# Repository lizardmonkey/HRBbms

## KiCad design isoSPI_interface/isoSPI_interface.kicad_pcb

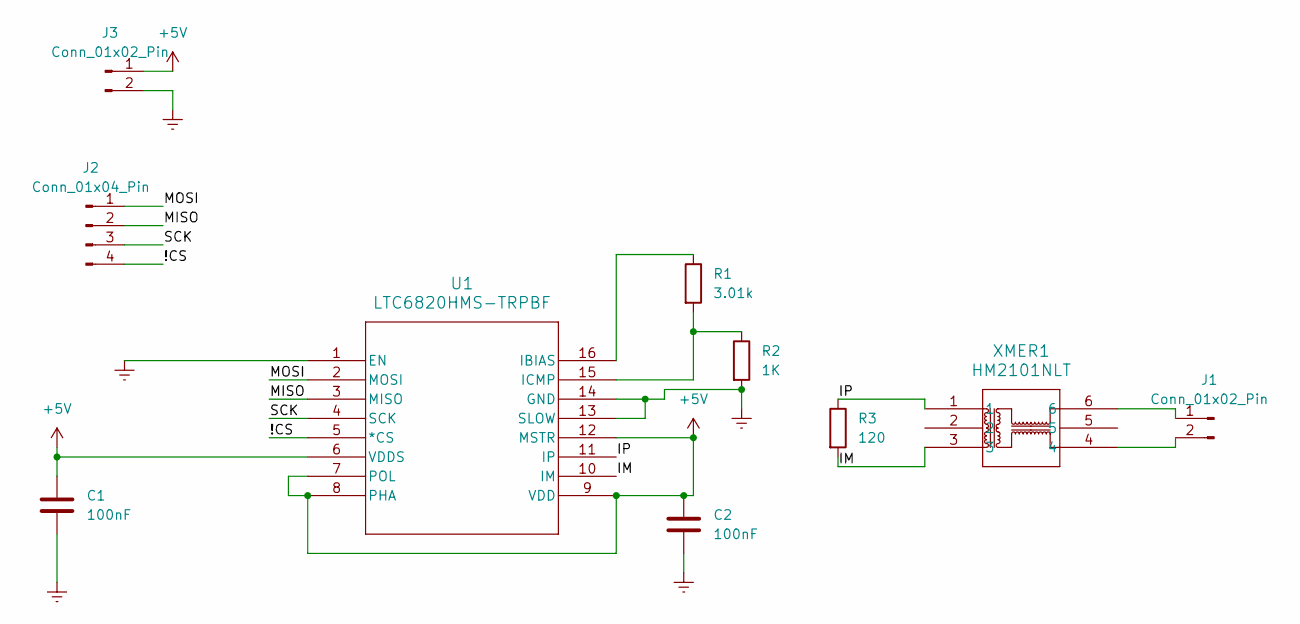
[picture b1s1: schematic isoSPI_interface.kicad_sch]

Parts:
C1, C2: 100nF; C_0805_2012Metric_Pad1.18x1.45mm_HandSolder
J1, J3: Conn_01x02_Pin; PinHeader_1x02_P2.54mm_Vertical
J2: Conn_01x04_Pin; PinHeader_1x04_P2.54mm_Vertical
R1: 3.01k; R_0805_2012Metric_Pad1.20x1.40mm_HandSolder
R2: 1K; R_0805_2012Metric_Pad1.20x1.40mm_HandSolder
R3: 120; R_0805_2012Metric_Pad1.20x1.40mm_HandSolder
U1: LTC6820HMS-TRPBF; MS_05-08-1669_ADI
XMER1: HM2101NLT; HM2101NLT_PUL

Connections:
+5V: C1.1, C2.1, J3.1, U1.6 (VDDS), U1.7 (POL), U1.8 (PHA), U1.9 (VDD), U1.12 (MSTR)
/!CS: J2.4, U1.5 (*CS)
/IM: R3.2, U1.10 (IM), XMER1.3
/IP: R3.1, U1.11 (IP), XMER1.1
/MISO: J2.2, U1.3 (MISO)
/MOSI: J2.1, U1.2 (MOSI)
/SCK: J2.3, U1.4 (SCK)
GNDREF: C1.2, C2.2, J3.2, R2.2, U1.1 (EN), U1.13 (SLOW), U1.14 (GND)
unnamed: J1.1, XMER1.6
unnamed: J1.2, XMER1.4
unnamed: R1.1, U1.16 (IBIAS)
unnamed: R1.2, R2.1, U1.15 (ICMP)

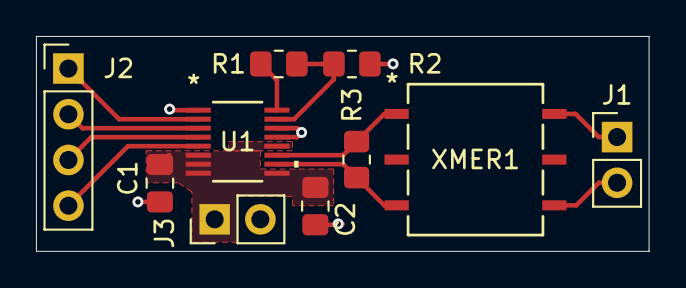
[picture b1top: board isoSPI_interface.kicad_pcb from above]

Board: 2 copper layers, 34.0 x 11.9 mm, 10 parts (0 on the bottom side), 12 nets.

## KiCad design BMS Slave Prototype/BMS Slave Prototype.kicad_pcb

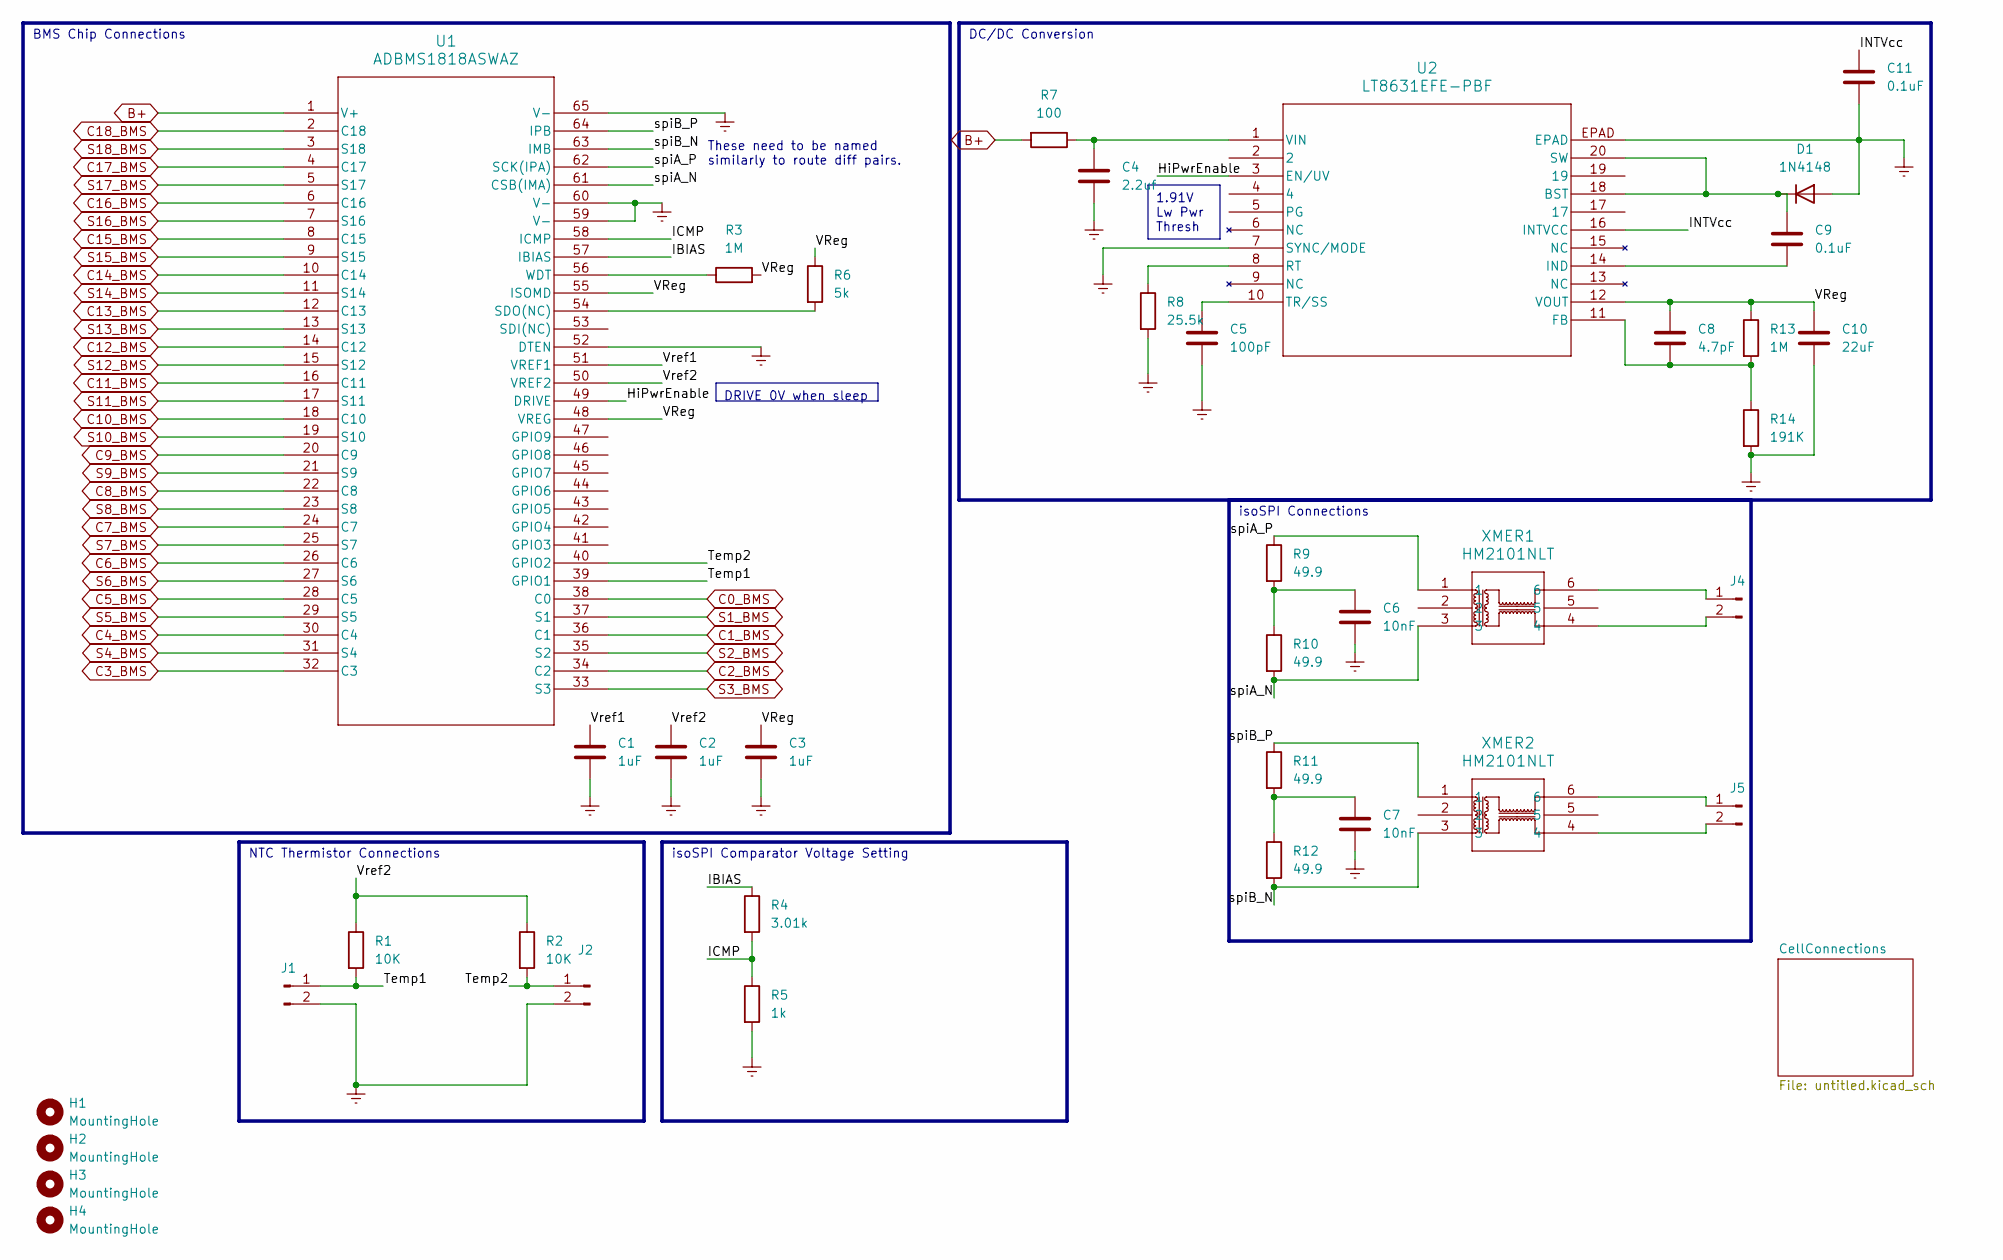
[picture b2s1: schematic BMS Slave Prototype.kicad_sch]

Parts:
C1, C2, C3: 1uF; C_0805_2012Metric
C4: 2.2uf; C_0805_2012Metric
C5: 100pF; C_0805_2012Metric
C6, C7: 10nF; C_0805_2012Metric
C8: 4.7pF; C_0805_2012Metric
C9, C11: 0.1uF; C_0805_2012Metric
C10: 22uF; C_0805_2012Metric
D1: 1N4148; D_SOD-323
H1, H2, H3, H4: MountingHole; MountingHole_2.7mm_M2.5
J1, J2, J4, J5: Conn_01x02_Pin; PinHeader_1x02_P2.54mm_Vertical
R1, R2: 10K; R_0805_2012Metric
R3, R13: 1M; R_0805_2012Metric
R4: 3.01k; R_0805_2012Metric
R5: 1k; R_0805_2012Metric
R6: 5k; R_0805_2012Metric
R7: 100; R_0805_2012Metric
R8: 25.5k; R_0805_2012Metric
R9, R10, R11, R12: 49.9; R_0805_2012Metric
R14: 191K; R_0805_2012Metric
U1: ADBMS1818ASWAZ; SW-64-2_ADI
U2: LT8631EFE-PBF; TSSOP-20_FE&slash_CB_LIT
XMER1, XMER2: HM2101NLT; HM2101NLT_PUL

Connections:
/HiPwrEnable: U1.49 (DRIVE), U2.3 (EN/UV)
/IBIAS: R4.1, U1.57 (IBIAS)
/ICMP: R4.2, R5.1, U1.58 (ICMP)
/INTVcc: C11.1, U2.16 (INTVCC)
/Temp1: J1.1, R1.2, U1.39 (GPIO1)
/Temp2: J2.1, R2.2, U1.40 (GPIO2)
/VReg: C3.1, C8.1, C10.1, R3.2, R6.1, R13.1, U1.48 (VREG), U1.55 (ISOMD), U2.12 (VOUT)
/Vref1: C1.1, U1.51 (VREF1)
/Vref2: C2.1, R1.1, R2.1, U1.50 (VREF2)
/spiA_N: R10.2, U1.61 (CSB(IMA)), XMER1.3
/spiA_P: R9.1, U1.62 (SCK(IPA)), XMER1.1
/spiB_N: R12.2, U1.63 (IMB), XMER2.3
/spiB_P: R11.1, U1.64 (IPB), XMER2.1
B+: R7.2, U1.1 (V+); also elsewhere on the board
C0_BMS: U1.38 (C0); also elsewhere on the board
C1_BMS: U1.36 (C1); also elsewhere on the board
C2_BMS: U1.34 (C2); also elsewhere on the board
C3_BMS: U1.32 (C3); also elsewhere on the board
C4_BMS: U1.30 (C4); also elsewhere on the board
C5_BMS: U1.28 (C5); also elsewhere on the board
C6_BMS: U1.26 (C6); also elsewhere on the board
C7_BMS: U1.24 (C7); also elsewhere on the board
C8_BMS: U1.22 (C8); also elsewhere on the board
C9_BMS: U1.20 (C9); also elsewhere on the board
C10_BMS: U1.18 (C10); also elsewhere on the board
C11_BMS: U1.16 (C11); also elsewhere on the board
C12_BMS: U1.14 (C12); also elsewhere on the board
C13_BMS: U1.12 (C13); also elsewhere on the board
C14_BMS: U1.10 (C14); also elsewhere on the board
C15_BMS: U1.8 (C15); also elsewhere on the board
C16_BMS: U1.6 (C16); also elsewhere on the board
C17_BMS: U1.4 (C17); also elsewhere on the board
C18_BMS: U1.2 (C18); also elsewhere on the board
GNDREF: C1.2, C2.2, C3.2, C4.2, C5.2, C6.2, C7.2, C10.2, C11.2, D1.2 (A), J1.2, J2.2, R5.2, R8.2, R14.2, U1.52 (DTEN), U1.59 (V-), U1.60 (V-), U1.65 (V-), U2.7 (SYNC/MODE), U2.EPAD; also elsewhere on the board
unnamed: C6.1, R9.2, R10.1
unnamed: C7.1, R11.2, R12.1
unnamed: C9.1, D1.1 (K), U2.18 (BST), U2.20 (SW)
unnamed: J4.1, XMER1.6
unnamed: J4.2, XMER1.4
unnamed: J5.1, XMER2.6
unnamed: J5.2, XMER2.4
unnamed: R6.2, U1.54 (SDO(NC))
unnamed: R3.1, U1.56 (WDT)
unnamed: C8.2, R13.2, R14.1, U2.11 (FB)
unnamed: C9.2, U2.14 (IND)
unnamed: R8.1, U2.8 (RT)
unnamed: C5.1, U2.10 (TR/SS)
unnamed: C4.1, R7.1, U2.1 (VIN)
S1_BMS: U1.37 (S1); also elsewhere on the board
S2_BMS: U1.35 (S2); also elsewhere on the board
S3_BMS: U1.33 (S3); also elsewhere on the board
S4_BMS: U1.31 (S4); also elsewhere on the board
S5_BMS: U1.29 (S5)
S6_BMS: U1.27 (S6)
S7_BMS: U1.25 (S7); also elsewhere on the board
S8_BMS: U1.23 (S8); also elsewhere on the board
S9_BMS: U1.21 (S9); also elsewhere on the board
S10_BMS: U1.19 (S10); also elsewhere on the board
S11_BMS: U1.17 (S11)
S12_BMS: U1.15 (S12)
S13_BMS: U1.13 (S13); also elsewhere on the board
S14_BMS: U1.11 (S14); also elsewhere on the board
S15_BMS: U1.9 (S15); also elsewhere on the board
S16_BMS: U1.7 (S16); also elsewhere on the board
S17_BMS: U1.5 (S17)
S18_BMS: U1.3 (S18)

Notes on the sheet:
1.91V Lw Pwr Thresh
DRIVE 0V when sleep
DC/DC Conversion
NTC Thermistor Connections
isoSPI Connections
BMS Chip Connections
isoSPI Comparator Voltage Setting
These need to be named similarly to route diff pairs.

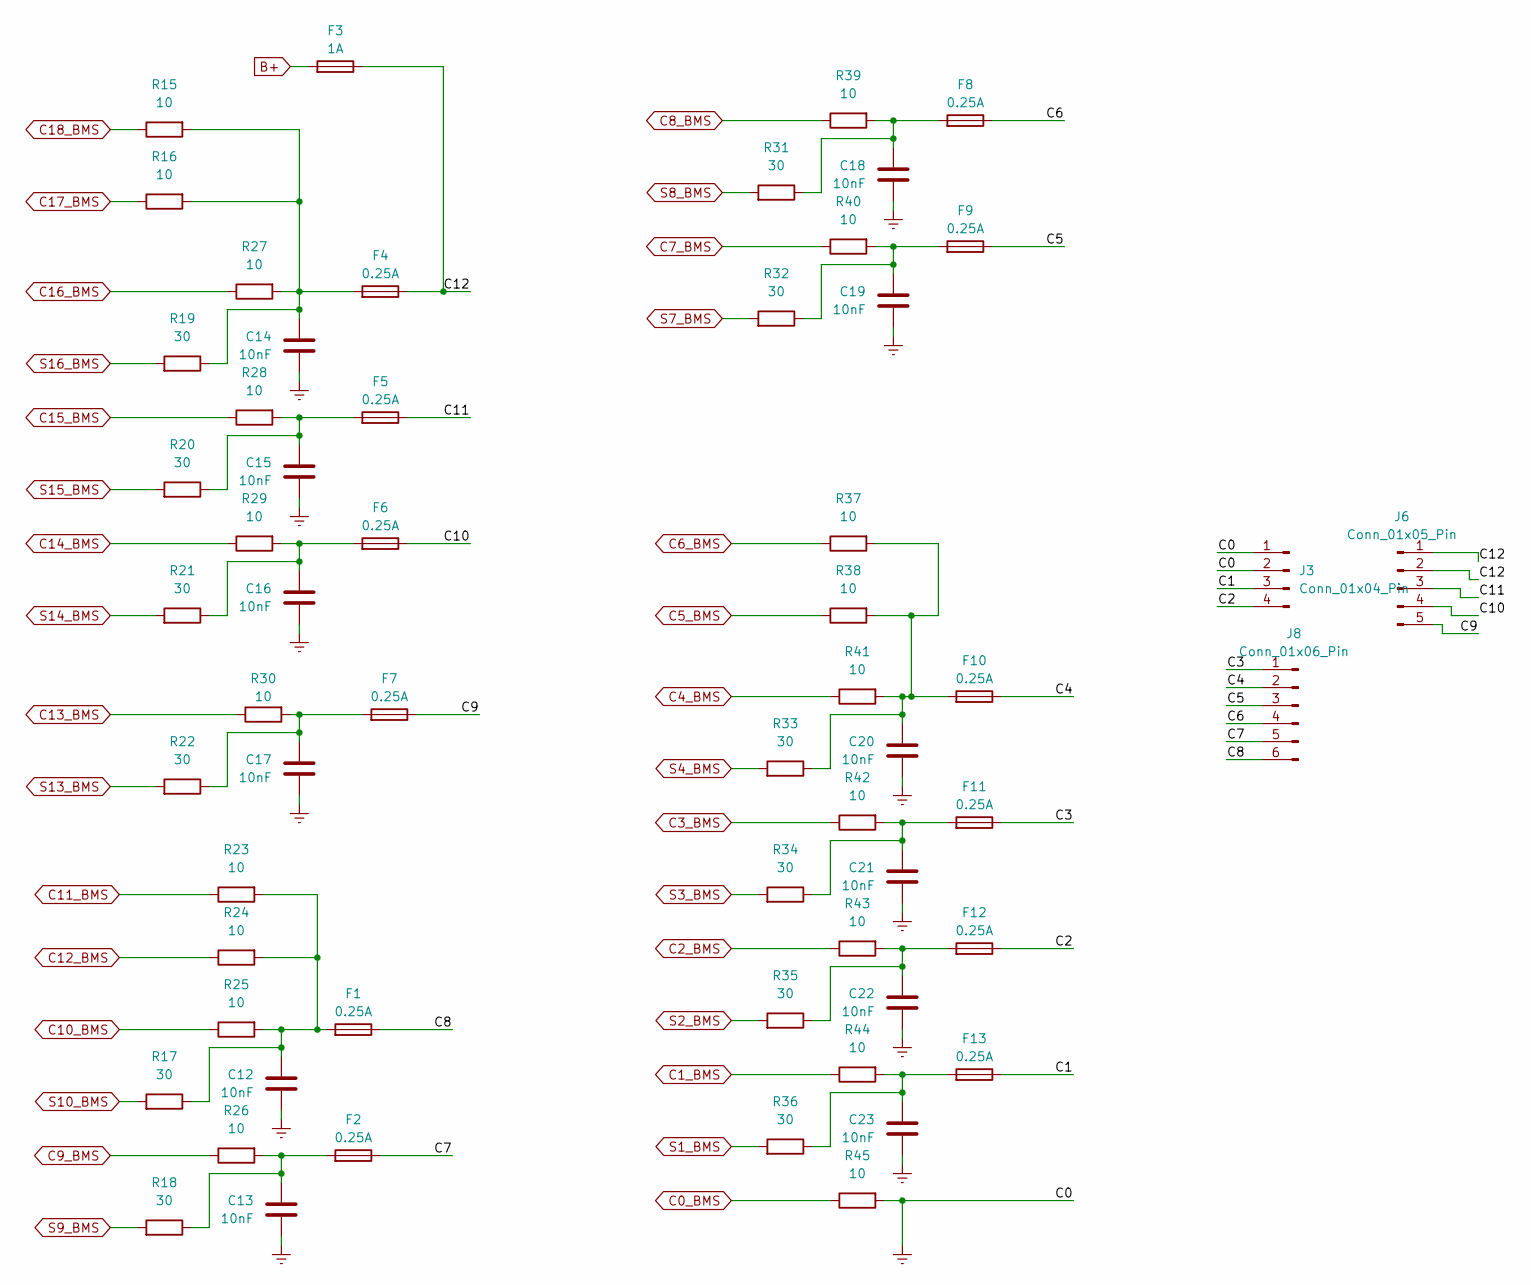
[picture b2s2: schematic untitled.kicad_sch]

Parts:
C12, C13, C14, C15, C16, C17, C18, C19, C20, C21, C22, C23: 10nF; C_0805_2012Metric
F1, F2, F4, F5, F6, F7, F8, F9, F10, F11, F12, F13: 0.25A; Fuse_0603_1608Metric
F3: 1A; Fuse_0603_1608Metric
J3: Conn_01x04_Pin; PinHeader_1x04_P2.54mm_Vertical
J6: Conn_01x05_Pin; PinHeader_1x05_P2.54mm_Vertical
J8: Conn_01x06_Pin; PinHeader_1x06_P2.54mm_Vertical
R15, R16, R23, R24, R25, R26, R27, R28, R29, R30, R37, R38, R39, R40, R41, R42, R43, R44, R45: 10; R_0805_2012Metric
R17, R18, R19, R20, R21, R22, R31, R32, R33, R34, R35, R36: 30; R_0805_2012Metric

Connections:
/CellConnections/C1: F13.1, J3.3
/CellConnections/C2: F12.1, J3.4
/CellConnections/C3: F11.1, J8.1
/CellConnections/C4: F10.1, J8.2
/CellConnections/C5: F9.1, J8.3
/CellConnections/C6: F8.1, J8.4
/CellConnections/C7: F2.1, J8.5
/CellConnections/C8: F1.1, J8.6
/CellConnections/C9: F7.1, J6.5
/CellConnections/C10: F6.1, J6.4
/CellConnections/C11: F5.1, J6.3
/CellConnections/C12: F3.1, F4.1, J6.1, J6.2
B+: F3.2; also elsewhere on the board
C0_BMS: R45.1; also elsewhere on the board
C1_BMS: R44.1; also elsewhere on the board
C2_BMS: R43.1; also elsewhere on the board
C3_BMS: R42.1; also elsewhere on the board
C4_BMS: R41.1; also elsewhere on the board
C5_BMS: R38.1; also elsewhere on the board
C6_BMS: R37.1; also elsewhere on the board
C7_BMS: R40.1; also elsewhere on the board
C8_BMS: R39.1; also elsewhere on the board
C9_BMS: R26.1; also elsewhere on the board
C10_BMS: R25.1; also elsewhere on the board
C11_BMS: R23.1; also elsewhere on the board
C12_BMS: R24.1; also elsewhere on the board
C13_BMS: R30.1; also elsewhere on the board
C14_BMS: R29.1; also elsewhere on the board
C15_BMS: R28.1; also elsewhere on the board
C16_BMS: R27.1; also elsewhere on the board
C17_BMS: R16.1; also elsewhere on the board
C18_BMS: R15.1; also elsewhere on the board
GNDREF: C12.2, C13.2, C14.2, C15.2, C16.2, C17.2, C18.2, C19.2, C20.2, C21.2, C22.2, C23.2, J3.1, J3.2, R45.2; also elsewhere on the board
unnamed: C12.1, F1.2, R17.1, R23.2, R24.2, R25.2
unnamed: C13.1, F2.2, R18.1, R26.2
unnamed: C14.1, F4.2, R15.2, R16.2, R19.1, R27.2
unnamed: C15.1, F5.2, R20.1, R28.2
unnamed: C16.1, F6.2, R21.1, R29.2
unnamed: C17.1, F7.2, R22.1, R30.2
unnamed: C18.1, F8.2, R31.1, R39.2
unnamed: C19.1, F9.2, R32.1, R40.2
unnamed: C20.1, F10.2, R33.1, R37.2, R38.2, R41.2
unnamed: C21.1, F11.2, R34.1, R42.2
unnamed: C22.1, F12.2, R35.1, R43.2
unnamed: C23.1, F13.2, R36.1, R44.2
S1_BMS: R36.2; also elsewhere on the board
S2_BMS: R35.2; also elsewhere on the board
S3_BMS: R34.2; also elsewhere on the board
S4_BMS: R33.2; also elsewhere on the board
S7_BMS: R32.2; also elsewhere on the board
S8_BMS: R31.2; also elsewhere on the board
S9_BMS: R18.2; also elsewhere on the board
S10_BMS: R17.2; also elsewhere on the board
S13_BMS: R22.2; also elsewhere on the board
S14_BMS: R21.2; also elsewhere on the board
S15_BMS: R20.2; also elsewhere on the board
S16_BMS: R19.2; also elsewhere on the board

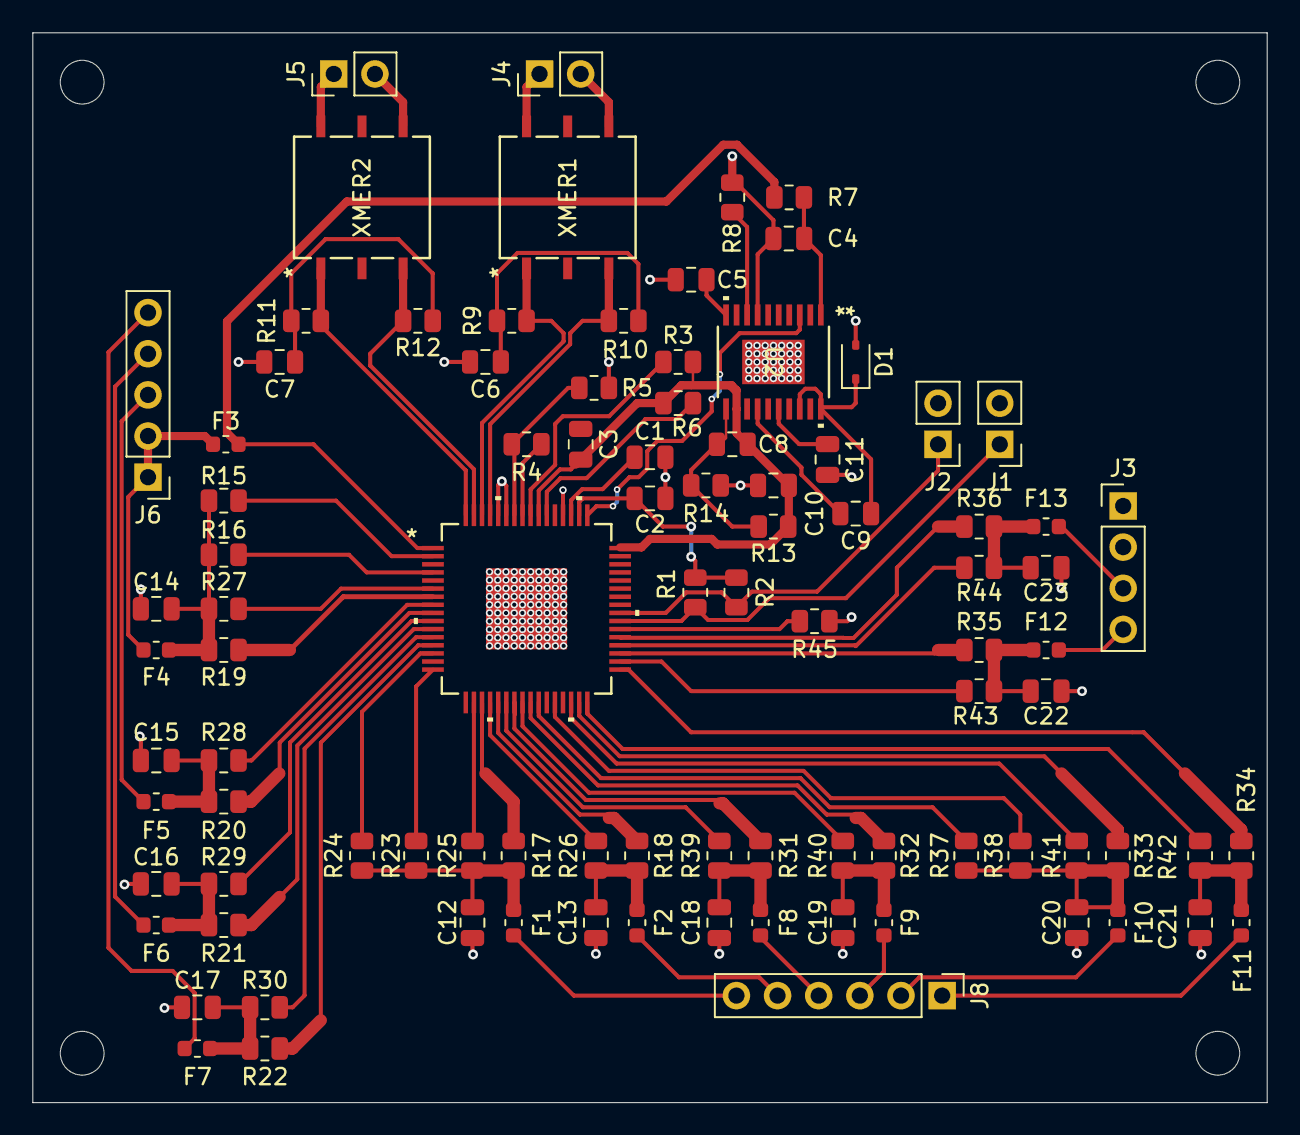
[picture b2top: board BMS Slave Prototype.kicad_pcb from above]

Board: 2 copper layers, 76.2 x 66.0 mm, 97 parts (0 on the bottom side), 84 nets.

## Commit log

2023-12-26 Initial Commit
    Include the prototype slave BMS board for 12 cells and the isoSPI interface test board.
